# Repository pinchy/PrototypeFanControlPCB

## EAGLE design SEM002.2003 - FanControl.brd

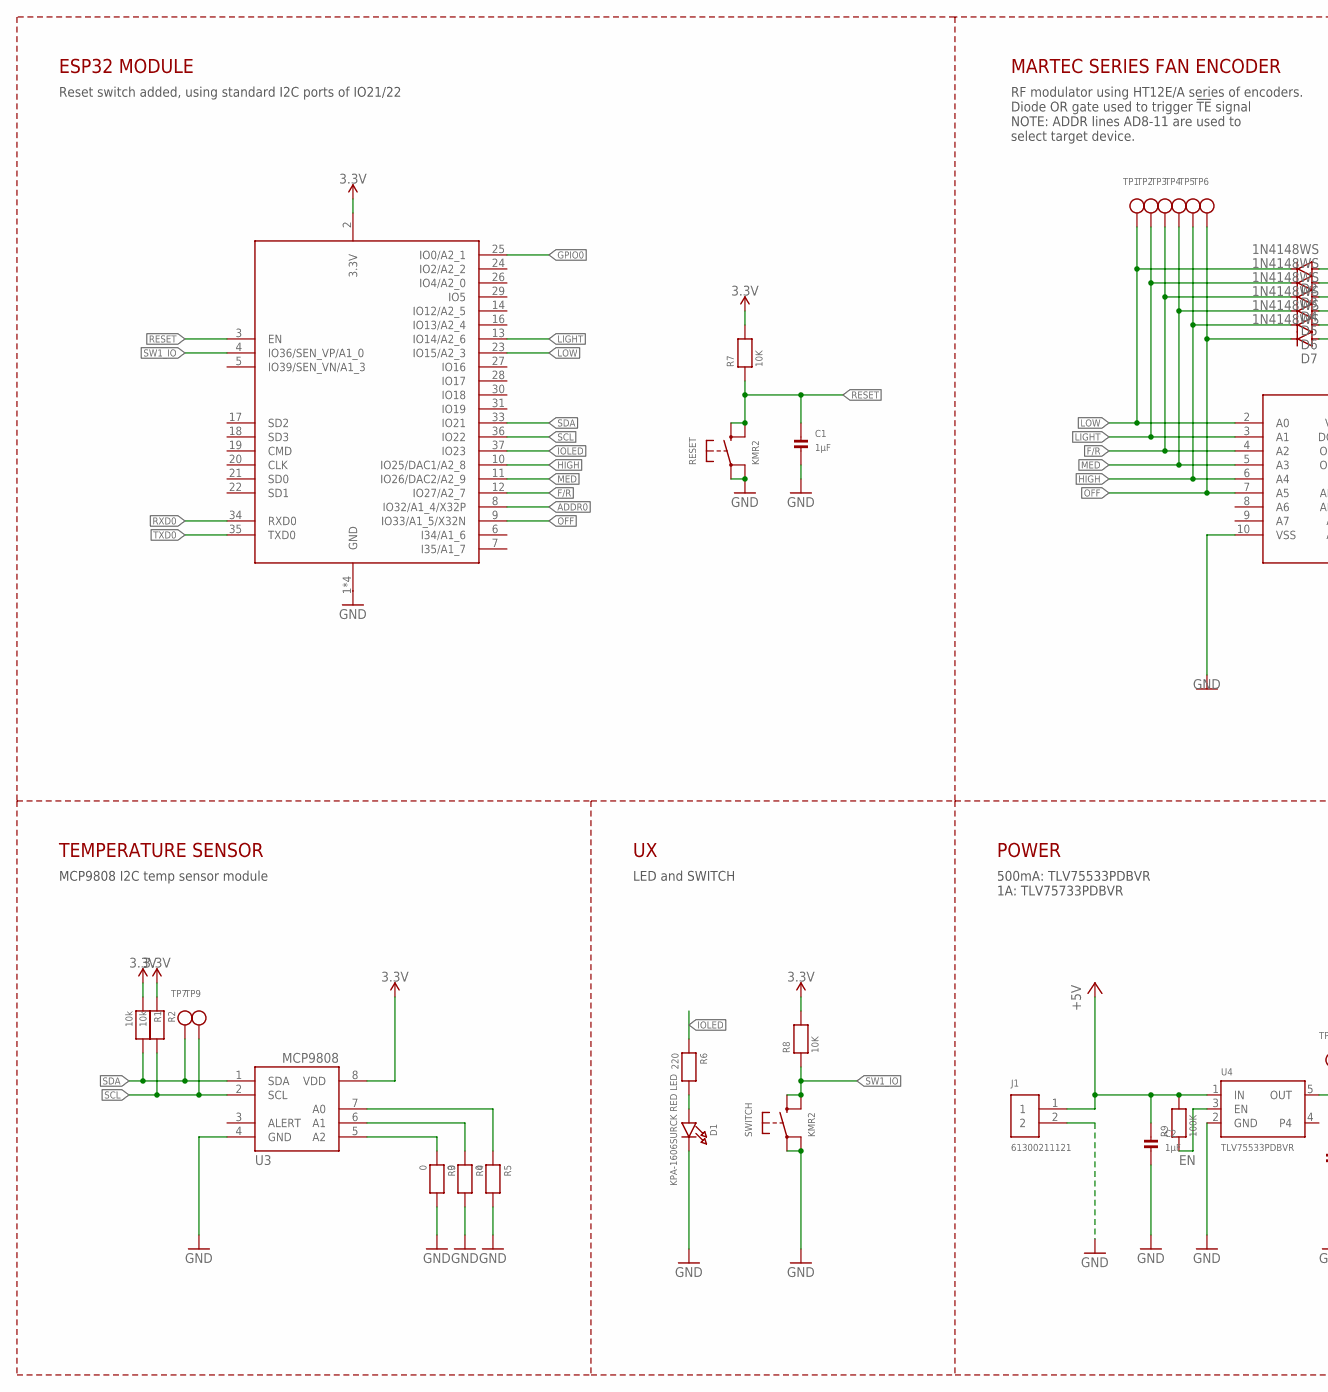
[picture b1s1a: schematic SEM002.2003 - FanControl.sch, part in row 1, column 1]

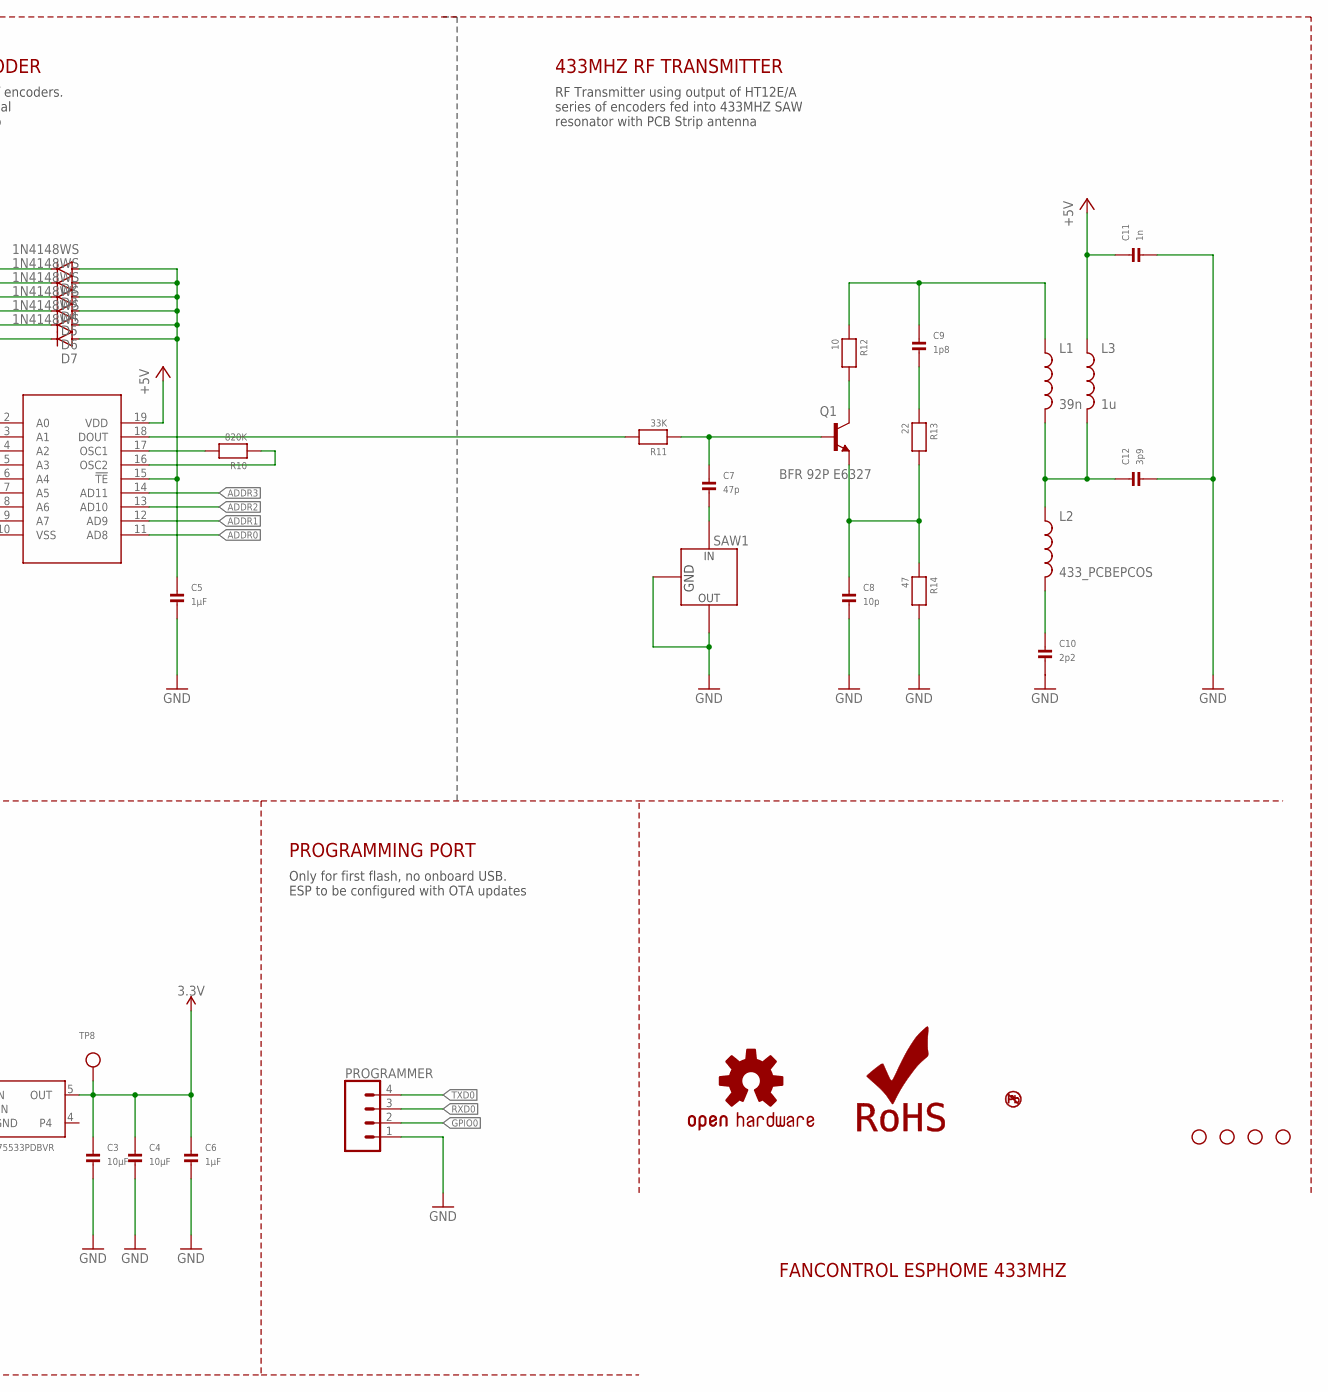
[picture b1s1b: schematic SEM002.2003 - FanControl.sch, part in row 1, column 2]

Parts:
C1, C6: 1µF; 0603; MPN LMK107B7105KA-T
C2: 1µF; 0805_NOTHERMALS; MPN LMK107B7105KA-T
C3: 10µF; 0603; MPN 0805YD106MAT4A
C4: 10µF; 0805_NOTHERMALS; MPN 0805YD106MAT4A
C5: 1µF; 0603-MINI; MPN LMK107B7105KA-T
C7: 47p; 0603-MINI; MPN 0603N470F500CT
C8: 10p; 0603-MINI; MPN 0603N100F500CT
C9: 1p8; 0603-MINI; MPN 0603N1R8B101CT
C10: 2p2; 0603-MINI; MPN 0603N2R2B101CT
C11: 1n; 0603-MINI; MPN 0603N102F500CT
C12: 3p9; 0603-MINI; MPN 0603N3R9B101CT
D1: KPA-1606SURCK RED LED; CHIPLED_0603; MPN SML-H12U8TT86C
D2, D3, D4, D5, D6, D7: 1N4148WS; SOD-323
H1, H2, H3, H4: STAND-OFF
J1: 61300211121
L1: 39n; L0603; MPN CI160808-39NJ
L2: 433_PCBEPCOS; 433MHZ-SAW
L3: 1u; L0603; MPN AIML-0603-1R0K-T
LOGO1: OSHW-LOGOM; OSHW-LOGO-M
LOGO2: ROHS_LOGO; ROHS_LOGO_0.18_IN
LOGO3: NO_PB_LOGO; NO_PB_LOGO_0.120
PROGRAMMER: CONN_04; 1X04
Q1: BFR 92P E6327; SOT23; MPN BFR92PE6327
R1, R2: 10k; 0603; MPN APC0603B10K0N
R3, R4, R5: 0; 0603; MPN CRCW06030000Z0EAC
R6: 220; 0603; MPN CRCW0603220RFKEAC
R7, R8: 10K; 0603; MPN APC0603B10K0N
R9: 100K; 0603-MINI; MPN CRCW0603100KFKEAC
R10: 820K; 0603; MPN ERJ-3EKF8203V
R11: 33K; 0603-MINI; MPN CRCW06033K30FKEAC
R12: 10; 0603-MINI; MPN RR0816Q-100-D
R13: 22; 0603-MINI; MPN RR0816Q-220-D
R14: 47; 0603-MINI; MPN ERA-3AED470V
RESET: KMR2; BTN_KMR2_4.6X2.8; MPN KMR221GLFS
SAW1: R727QCC8C; QCC8C; MPN B39431B3730H110
SWITCH: KMR2; BTN_KMR2_4.6X2.8; MPN KMR221GLFS
TP1, TP2, TP3, TP4, TP5, TP6, TP7, TP9: TESTPOINTROUND1MM; TESTPOINT_ROUND_1MM; MPN DNL
TP8: TESTPOINTROUND1MM; TESTPOINT_ROUND_1MM
U1: ESP32_WROOM32_SKINNY; WROOM32_SKINNY; MPN ESP32-WROOM-32
U2: HT12ESO20; SO20_SOT163-1-R; MPN HT12E-20SOP
U3: MCP9808-E/MS; MSOP8_0.65MM; MPN MCP9808-E/MS
U4: TLV75533PDBVR; SOT23-5; MPN TLV75733PDBVR

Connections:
3.3V: C3.1, C4.1, C6.1, R1.1, R2.1, R7.2, R8.2, TP8.P$1, U1.2 (3.3V), U3.8 (VDD), U4.5 (OUT)
+5V: C2.1, C11.1, J1.1, L3.1, R9.2, U2.19 (VDD), U4.1 (IN)
ADDR0: U1.8 (IO32/A1_4/X32P), U2.11 (AD8)
ADDR1: U2.12 (AD9)
ADDR2: U2.13 (AD10)
ADDR3: U2.14 (AD11)
EN: R9.1, U4.3 (EN)
F/R: D4.C, TP3.P$1, U1.12 (IO27/A2_7), U2.4 (A2)
GND: C1.2, C2.2, C3.2, C4.2, C5.2, C6.2, C8.2, C10.2, C11.2, C12.2, D1.C, J1.2, PROGRAMMER.1, R3.2, R4.2, R5.2, R14.2, RESET.A, RESET.A' (P1), SAW1.P$1, SAW1.P$3, SAW1.P$4, SAW1.P$5, SAW1.P$6, SWITCH.A, SWITCH.A' (P1), U1.1 (GND), U1.15 (GND), U1.38 (GND), U1.P$1 (GND), U2.10 (VSS), U3.4 (GND), U4.2 (GND)
GPIO0: PROGRAMMER.2, U1.25 (IO0/A2_1)
HIGH: D6.C, TP5.P$1, U1.10 (IO25/DAC1/A2_8), U2.6 (A4)
IOLED: R6.1, U1.37 (IO23)
LIGHT: D3.C, TP2.P$1, U1.13 (IO14/A2_6), U2.3 (A1)
LOW: D2.C, TP1.P$1, U1.23 (IO15/A2_3), U2.2 (A0)
MED: D5.C, TP4.P$1, U1.11 (IO26/DAC2/A2_9), U2.5 (A3)
unnamed: R5.1, U3.7 (A0)
unnamed: C5.1, D2.A, D3.A, D4.A, D5.A, D6.A, D7.A, U2.15 (!TE!)
unnamed: R4.1, U3.6 (A1)
unnamed: R10.2, U2.17 (OSC1)
unnamed: D1.A, R6.2
unnamed: R10.1, U2.16 (OSC2)
unnamed: R3.1, U3.5 (A2)
unnamed: R11.2, U2.18 (DOUT)
unnamed: C7.1, Q1.1 (B), R11.1
unnamed: Q1.3 (C), R12.2
unnamed: C9.2, R13.1
unnamed: C8.1, Q1.2 (E), R13.2, R14.1
unnamed: C7.2, SAW1.P$2
unnamed: C9.1, L1.1, R12.1
unnamed: C12.1, L1.2, L2.P$1 (1), L3.2
unnamed: C10.1, L2.P$2 (2)
OFF: D7.C, TP6.P$1, U1.9 (IO33/A1_5/X32N), U2.7 (A5)
RESET: C1.1, R7.1, RESET.B (S), RESET.B' (S1), U1.3 (EN)
RXD0: PROGRAMMER.3, U1.34 (RXD0)
SCL: R2.2, TP9.P$1, U1.36 (IO22), U3.2 (SCL)
SDA: R1.2, TP7.P$1, U1.33 (IO21), U3.1 (SDA)
SW1_IO: R8.1, SWITCH.B (S), SWITCH.B' (S1), U1.4 (IO36/SEN_VP/A1_0)
TXD0: PROGRAMMER.4, U1.35 (TXD0)

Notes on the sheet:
500mA: TLV75533PDBVR 1A: TLV75733PDBVR
MARTEC SERIES FAN ENCODER
RF modulator using HT12E/A series of encoders. Diode OR gate used to trigger !TE! signal NOTE: ADDR lines AD8-11 are used to select target device.
433MHZ RF TRANSMITTER
RF Transmitter using output of HT12E/A series of encoders fed into 433MHZ SAW resonator with PCB Strip antenna
TEMPERATURE SENSOR
MCP9808 I2C temp sensor module
POWER
ESP32 MODULE
Reset switch added, using standard I2C ports of IO21/22
Only for first flash, no onboard USB. ESP to be configured with OTA updates
PROGRAMMING PORT
LED and SWITCH

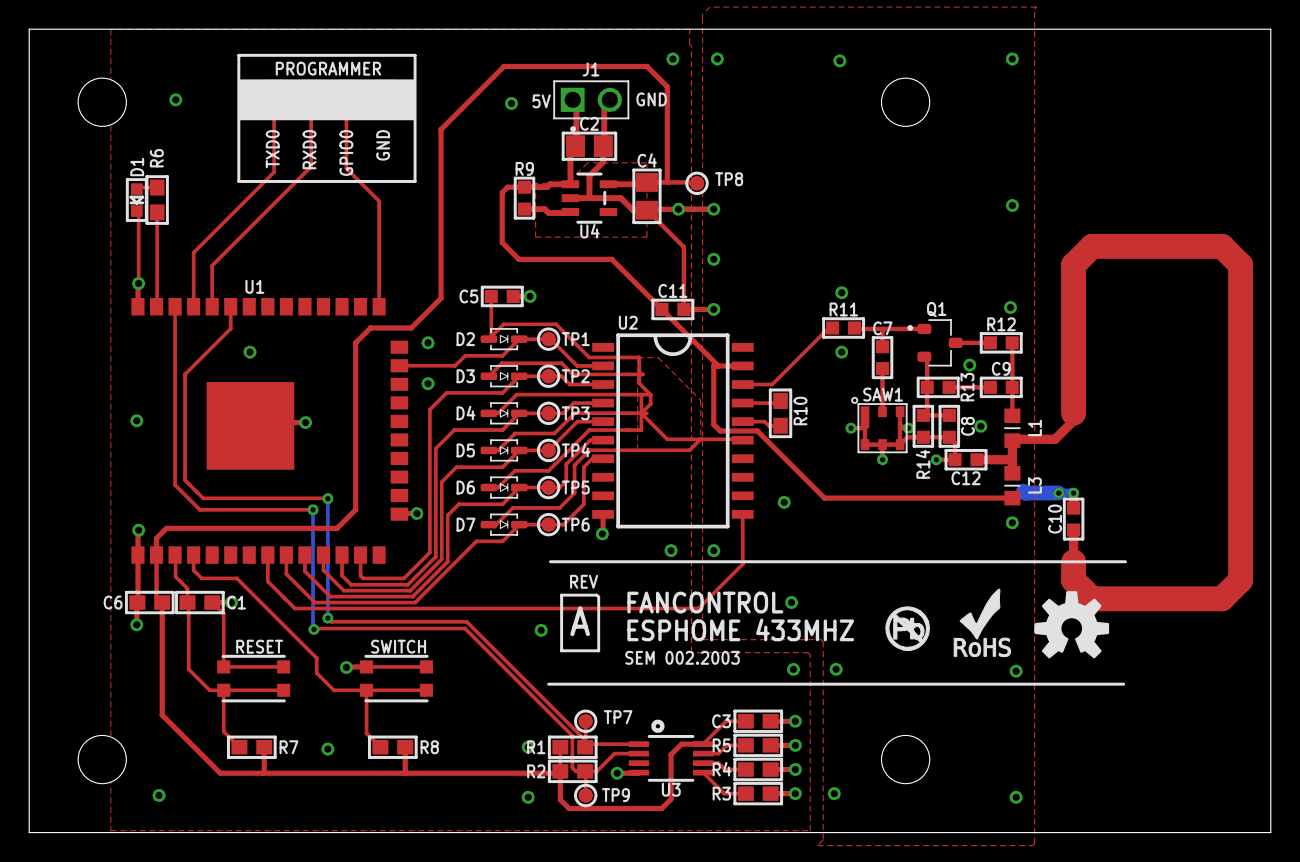
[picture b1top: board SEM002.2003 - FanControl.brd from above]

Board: 2 copper layers, 85.0 x 55.0 mm, 62 parts (0 on the bottom side), 35 nets.

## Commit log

2020-03-23 Initial Push

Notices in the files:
parts and their libraries:
microbuilder: This work is placed in the public domain, and may be freely used for commercial and non-commercial work with the following conditions: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
SparkFun-Hardware: Licensing: Creative Commons ShareAlike 4.0 International - https://creativecommons.org/licenses/by-sa/4.0
